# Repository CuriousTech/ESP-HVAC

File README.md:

# ESP-HVAC (ESP8266 & ESP-32)
WiFi Smart Omniscient HVAC Touchscreen Theromstat  

This project is discontinued (except for bugfixes and support code changes). New work will be on 
[WT32-SC01-HVAC](https://github.com/CuriousTech/WT32-SC01-HVAC)  

<b>2018 Model:</b> The new model was redesigned with a cooler switching regulator (~20mA idle, with a dim screen), smaller ($16.50 from OSHPark) more options for the temp/RH sensor, and the rotory encoder was removed, but has a header for an external encoder or buttons. The only difference in connections is the SCL/SDA were accidentaly reversed on the onboard SHTxx chip. Pics should be at the bottom.  

Notes about the Nextion: The baudrate is bauds=115200 in the main initialize varaibles. This will allow it to communicate at the highest speed.  

The "Basic" (Discovery model works without modification) has a 10K pullduown resistor for 5V tolerance (R13: next to the connector).  Removing this allows the ESP8266 to boot normally and operate without any resistors added, or add a 10K pullup between TX and 3V3 when serial debug is not connected.  I've opted for the removal of the resistor, which fixes all problems.  The 5K6 on the thermostat (R17) allowed it to operate with serial connected plus the pulldown, but not without.  The blue wire (data sent to the ESP) doesn't really need any resistors.  The ESP can't be programmed without a 1K while both are connected, and with the 1K and debug the touchscreen won't work.  So just disconnect the wire while programming and reconnect it after.  

This has replaced the old Spark-O-Stat with a newer system using the ESP-07 (now ESP32), with a better screen (Nextion HMI 2.8" touchscreen), 5 outputs (1 extra output for humidifier), option for SHT21 (I2C) or DHT22/11, AM2302/22, and anolog input for expansion.  

Main and remote units are designed into the single PCB with wired 5V or USB Mini-B for the remote units, and 24VAC for main.  Headers on top are for onboard serial programming of the ESP and Nextion.  Only power it with 1 source at a time. (3V3 for just the ESP, encoder, and temp sensor, 5V to include the display, or 24VAC for all of it including the SSRs). Add the switching regulator to the remote for battery power (6-40V).   

<b>Remote:</b> By tapping the target temperature on the display, it will toggle transmitting the remote temperature and humidity to the main unit to use in all operations.  Tapping the same item on the main unit will also end the remote temperature connection.  There are notifications to indicate use as well as a flashing run indicator instead of solid.  

Some screens including a keyboard and SSID chooser, but this is using the auto connect with SoftAP server (which attempts to find the stored SSID while waiting on input) so it should never be needed.  The dimmed screensaver will change to a clock, and a few other odd displays over time.  

Cool/heat low/high:  
These are the desired temperature ranges for cooling and heating, which are calculated based on outside temperature over the next set number of days.  

Cycle:  
Disable heat and cool, but still cycles the fan by the Auto Fan: Run: settings. 4:00 and 5 default = 5 minutes every 4 hours.  

Threshold:  
The temperature offset to complete a cycle.  

Pre-cycle fan time:  
0 disables, 1 second to 5 minutes.  This is the first phase of the cycle.  When the temperature reaches the target, the fan is turned on to cycle air for the set time, which causes the thermostat to read a more overall temperature. If the threshold is reached before this ends, which it can, it will shut off. Otherwise it continues to the run phase, which runs for at least the cycleMin period to save wear on the compressor because this does shorten the run time considerably.  A good value to use is the time it takes to lower the temperature after turning the fan on before it plateaus.  Usually around 2 minutes.  

Post-cycle fan time:  
Runs fan after cycle completes.  This is the third phase of the cycle, which continues to push air through the cold radiator and ductwork.  2 minutes is good, but you can use an IR thermometer on a vent to see how long the cold air continues.  

Humidifier settings:  
Off: Always off  
Fan: Run when fan is on  
Run: Run when thermostat is running a cycle  
Auto1: Operate by humidistat during run cycles  
Auto2: Humidistat runs indepentantly of thermostat (shares fan control)  

Override:  
Use to heat or cool by a selected offset temperature for a specified time.  

Freshen:  
Starts the fan with a timeout.  This uses the post fan timer, so a normal cycle will cancel it.  

Idle min, cycle min/max:  
These are timers in seconds to control the thermstat operating limits.  Idle min is the shortest time between cycles.  Cycle min is the shortest time for a cycle, and max is the longest.  Be careful with these settings.  Running the compressor too short or too long can cause damage.  

Away time and temperature delta offset:  
The away time is in hours:minutes unlike the rest of the timers, but uses the override timer.  It can be turned on and off with the button, but will also turn off with the timer.  There are 2 temp values that are displayed depending on heat or cool mode.  One for heat and one for cool, like the pre/post fan.
Like any setting, it can be automated with something like Tasker.  To turn on would be <b>http://ip:85?key=password&away=1</b>  

Other settings:  
AC differential limit: Increases thermostat if inside/outside difference is more than 30. This assumes Fahrenheit. Change for Celcius.  
Heat Threshold: Heatpump will switch off and use gas when outside temp goes below set value (default 33). Change for Celcius.  
PKW (price per killawatt hour), CFM (gas cubic feet per minute), CCF (cost per 100 cubic foot): Set the PPKW and CCF based on billing. CFM is dependant on the furnace.  
FC Shift (in minutes): Shifts the forecast for the temperature adjust. Use the setting on the chart page (they don't affect the actual settings) to determine what's best. There are 2 values for heat and cool here as well.   

The web chart.  Dark gray is off, cyan is fan running, blue is compressor+fan, NG is red, HP is yellow, rh is green, the target/threshold is the wave.  The thermostat is in the hottest room in the house, so it does look warmer than it really is, but that's why there's a remote unit, and now multiple sensors.  

New Model
  
Remote (this uses only a few components: the 3.3V regulator, 3 capacitors, USB connector, temp sensor, and 7 required resistors)  

Sensor web page

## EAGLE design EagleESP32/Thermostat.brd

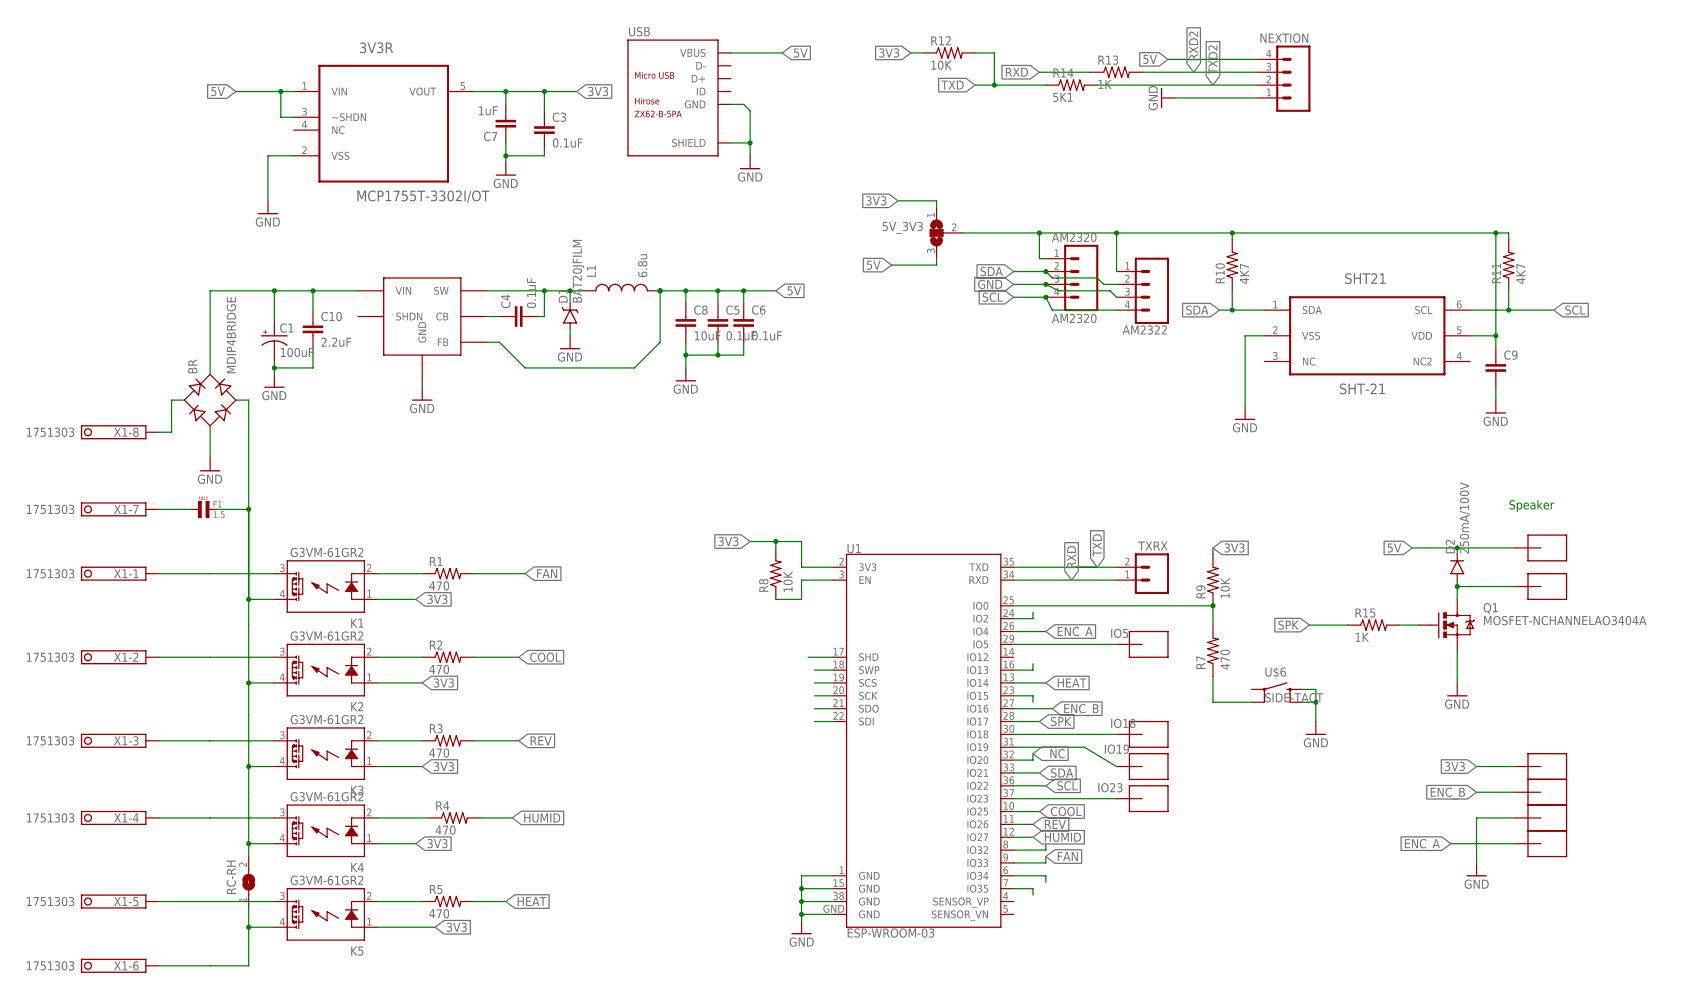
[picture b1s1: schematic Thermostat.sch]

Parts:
3V3R: MCP1755T-3302I/OT; SOT95P270X145-5N
5V_3V3: SJ2W; SJ_2
AM2320: AM2320; 1X04
AM2322: CONN_041.27MM; 1X04_1.27MM
BR: MDIP4BRIDGE; MICRODIP4
C1: 100uF; PANASONIC_C
C3, C4, C5, C6: 0.1uF; 0805
C7: 1uF; 0805
C8: 10uF; 0805
C9: CAP0603-CAP; 0603-CAP
C10: 2.2uF; 0805
D1: BAT20JFILM; SOD-323
D2: 250mA/100V; SOD-323
F1: 1.5; L4,8
K1, K2, K3, K4, K5: G3VM-61GR2; SOP04
L1: 6.8u; 1007
NEXTION: M04PTH; 1X04
Q1: MOSFET-NCHANNELAO3404A; SOT23-3
R1, R2, R3, R4, R5, R7: 470; 0805
R8, R9, R12: 10K; 0805
R10, R11: 4K7; 0805
R13, R15: 1K; 0805
R14: 5K1; 0805
RC-RH: SJ
SHT21: SHT-21; SHT21
TXRX: M02PTH; 1X02
U1: ESP-WROOM-03
U$1, U$2, U$3, U$4: SMD-PAD182X64; SMD-PAD1
U$5, U$7, U$8, U$9, U$10, U$11: SMD-PAD1SMD-PAD80X32; SMD-PAD6
U$6: SIDE-TACT
USB: ZX62-B-5PA; MICRO-USB5+6P-SMD-0.65-AB
VREG: LMR16006YQ; SOT-23-6
X1: 1751303

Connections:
3V3: 3V3R.5 (VOUT), 5V_3V3.1, C3.1, C7.2, K1.1 (A), K2.1 (A), K3.1 (A), K4.1 (A), K5.1 (A), R8.2, R9.2, R12.1, U1.2 (3V3), U$7.>PAD
5V: 3V3R.1 (VIN), 3V3R.3 (~SHDN), 5V_3V3.3, C5.1, C6.1, C8.1, D2.C, L1.2, NEXTION.4, U$5.>PAD, USB.1 (VBUS), VREG.3 (FB)
COOL: R2.2, U1.10 (IO25)
ENC_A: U1.26 (IO4), U$10.>PAD
ENC_B: U1.27 (IO16), U$8.>PAD
FAN: R1.2, U1.9 (IO33)
GND: 3V3R.2 (VSS), AM2320.3, AM2322.3, BR.-, C1.-, C3.2, C5.2, C6.2, C7.1, C8.2, C9.2, C10.2, D1.A, NEXTION.1, Q1.2 (S), SHT21.2 (VSS), U1.1 (GND), U1.15 (GND), U1.38 (GND), U1.GND, U$6.3 (2), U$6.4, U$9.>PAD, USB.5 (GND), USB.P1 (SHIELD), USB.P2 (SHIELD), USB.P3 (SHIELD), USB.P4 (SHIELD), USB.P5 (SHIELD), USB.P6 (SHIELD), VREG.2 (GND)
HEAT: R5.2, U1.13 (IO14)
HUMID: R4.2, U1.12 (IO27)
IO5: U1.29 (IO5), U$3.>PAD
IO18: U1.30 (IO18), U$4.>PAD
IO19: U1.31 (IO19), U$1.>PAD
IO23: U1.37 (IO23), U$2.>PAD
unnamed: C4.2, D1.C, L1.1, VREG.6 (SW)
unnamed: BR.AC2, F1.P$2 (2), K1.4 (DS1), K2.4 (DS1), K3.4 (DS1), K4.4 (DS1), RC-RH.2
unnamed: K4.2 (K), R4.1
unnamed: Q1.1 (G), R15.2
unnamed: K3.2 (K), R3.1
unnamed: R8.1, U1.3 (EN)
unnamed: K2.2 (K), R2.1
unnamed: K4.3 (DS2), X1.4
unnamed: K2.3 (DS2), X1.2
unnamed: R7.2, R9.1, U1.25 (IO0)
unnamed: K1.3 (DS2), X1.1
unnamed: K1.2 (K), R1.1
unnamed: C4.1, VREG.1 (CB)
unnamed: K5.3 (DS2), X1.5
unnamed: BR.AC1, X1.8
unnamed: K5.4 (DS1), RC-RH.1, X1.6
unnamed: F1.P$1 (1), X1.7
unnamed: BR.+, C1.+, C10.1, VREG.5 (VIN)
unnamed: K5.2 (K), R5.1
unnamed: R7.1, U$6.2 (3)
unnamed: K3.3 (DS2), X1.3
unnamed: D2.A, Q1.3 (D), U$11.>PAD
NC: SHT21.3 (NC)
PWR: 5V_3V3.2, AM2320.1, AM2322.1, C9.1, R10.2, R11.2, SHT21.5 (VDD)
REV: R3.2, U1.11 (IO26)
RXD: R13.1, TXRX.1, U1.34 (RXD)
RXD2: NEXTION.3, R13.2
SCL: AM2320.4, AM2322.4, R11.1, SHT21.6 (SCL), U1.36 (IO22)
SDA: AM2320.2, AM2322.2, R10.1, SHT21.1 (SDA), U1.33 (IO21)
SPK: R15.1, U1.28 (IO17)
TXD: R12.2, R14.1, TXRX.2, U1.35 (TXD)
TXD2: NEXTION.2, R14.2
_NC: U1.32 (IO20)

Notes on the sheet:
Speaker

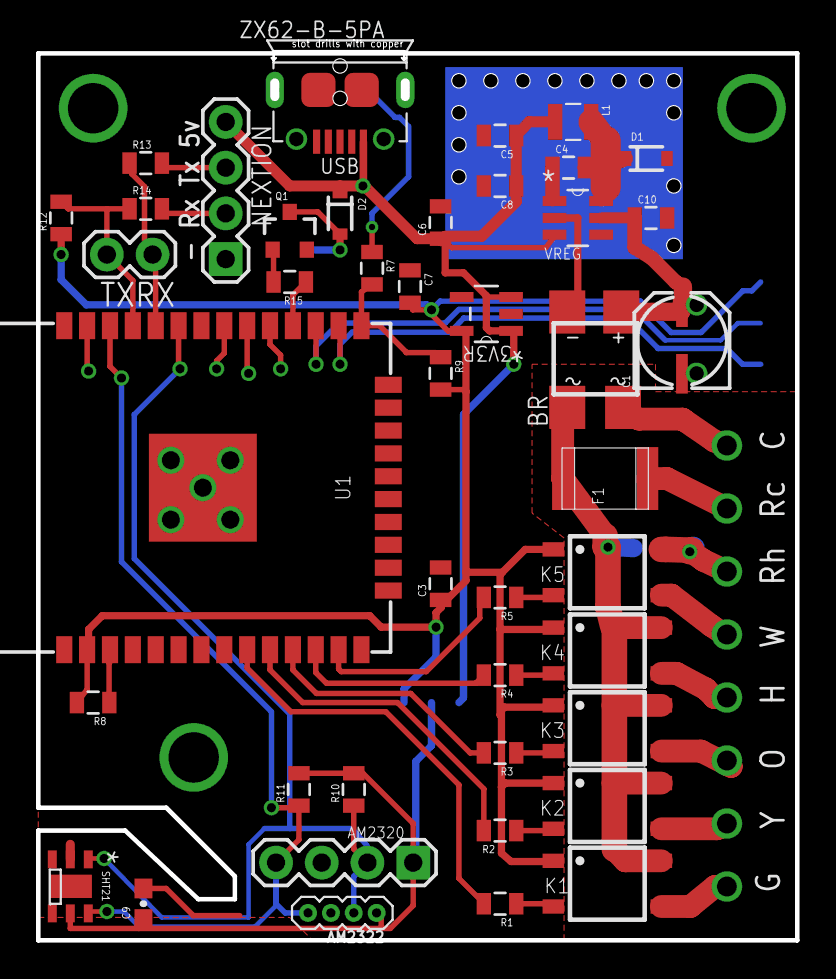
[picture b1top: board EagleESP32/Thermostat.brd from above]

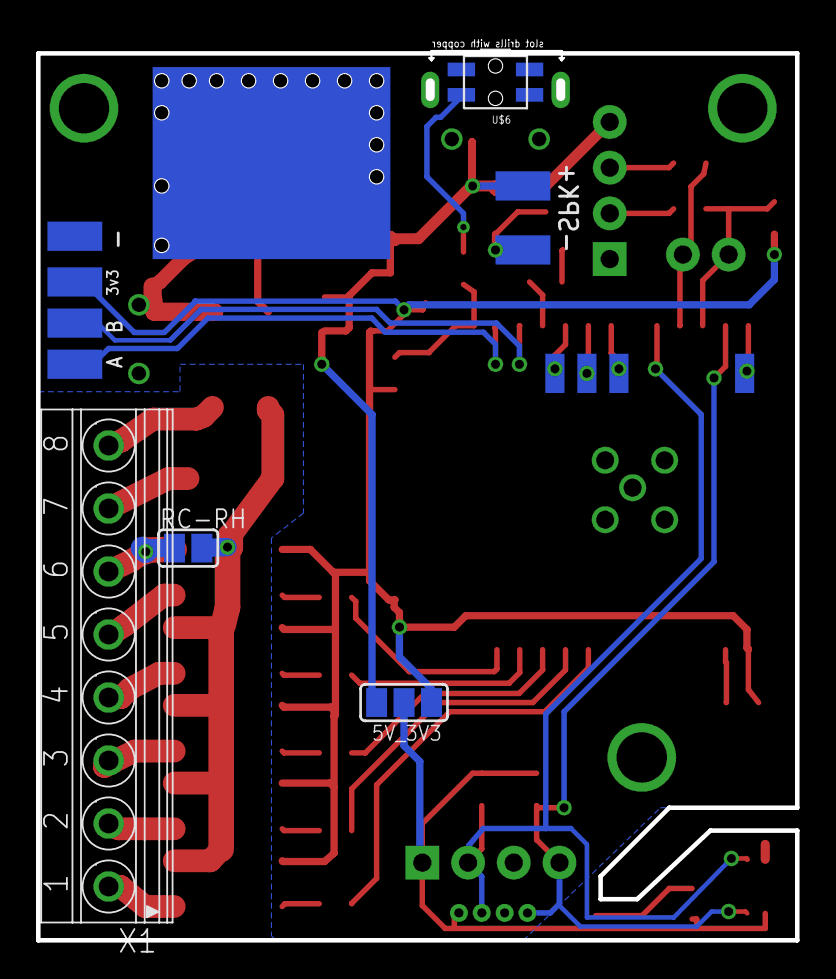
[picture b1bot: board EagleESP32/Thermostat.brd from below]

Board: 2 copper layers, 41.9 x 49.9 mm, 57 parts (14 on the bottom side), 44 nets.

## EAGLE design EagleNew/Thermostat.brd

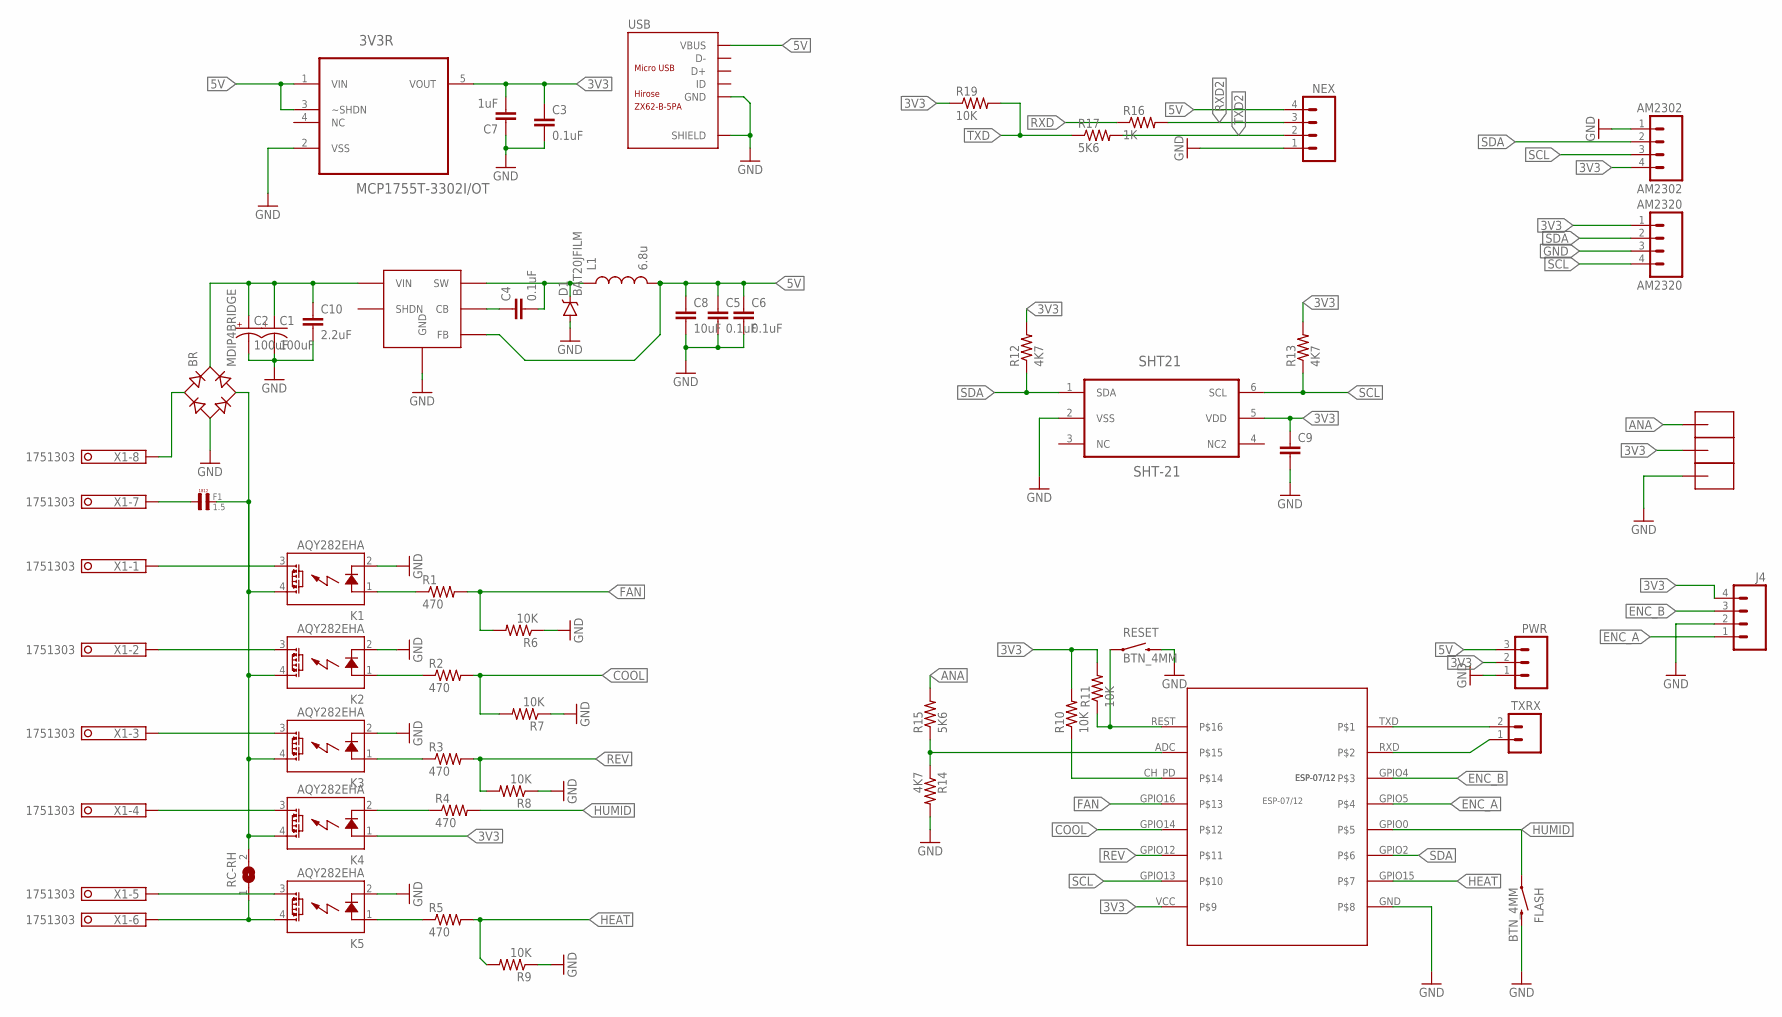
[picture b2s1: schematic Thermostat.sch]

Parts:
3V3R: MCP1755T-3302I/OT; SOT95P270X145-5N
AM2302: AM2302; 1X04
AM2320: AM2320; 1X04
BR: MDIP4BRIDGE; MICRODIP4
C1, C2: 100uF; PANASONIC_C
C3, C4, C5, C6: 0.1uF; 0805
C7: 1uF; 0805
C8: 10uF; 0805
C9: CAP0603-CAP; 0603-CAP
C10: 2.2uF; 0805
D1: BAT20JFILM; SOD-323
F1: 1.5; L4,8
FLASH: BTN_4MM
J4: M04PTH; 1X04
K1, K2, K3, K4, K5: AQY282EHA; SOP04
L1: 6.8u; 1007
NEX: M04PTH; 1X04
PWR: M03PTH; 1X03
R1, R2, R3, R4, R5: 470; 0805
R6, R7, R8, R9, R10, R11, R19: 10K; 0805
R12, R13, R14: 4K7; 0805
R15, R17: 5K6; 0805
R16: 1K; 0805
RC-RH: SJ
RESET: BTN_4MM
SHT21: SHT-21; SHT21
TXRX: M02PTH; 1X02
U$1: ESP-07/12
U$2, U$3, U$4: SMD-PAD182X64; SMD-PAD1
USB: ZX62-B-5PA; MICRO-USB5+6P-SMD-0.65-AB
VREG: LMR16006YQ; SOT-23-6
X1: 1751303

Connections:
3V3: 3V3R.5 (VOUT), AM2302.4, AM2320.1, C3.1, C7.2, C9.1, J4.4, K4.1 (A), PWR.2, R10.2, R11.2, R12.2, R13.2, R19.1, SHT21.5 (VDD), U$1.VCC, U$3.>PAD
5V: 3V3R.1 (VIN), 3V3R.3 (~SHDN), C5.1, C6.1, C8.1, L1.2, NEX.4, PWR.3, USB.1 (VBUS), VREG.3 (FB)
ADC: R14.1, R15.1, U$1.ADC
ANA: R15.2, U$4.>PAD
COOL: R2.2, R7.2, U$1.GPIO14
ENC_A: J4.1, U$1.GPIO5
ENC_B: J4.3, U$1.GPIO4
FAN: R1.2, R6.2, U$1.GPIO16
GND: 3V3R.2 (VSS), AM2302.1, AM2320.3, BR.-, C1.-, C2.-, C3.2, C5.2, C6.2, C7.1, C8.2, C9.2, C10.2, D1.A, FLASH.2, J4.2, K1.2 (K), K2.2 (K), K3.2 (K), K5.2 (K), NEX.1, PWR.1, R6.1, R7.1, R8.1, R9.1, R14.2, RESET.2, SHT21.2 (VSS), U$1.GND, U$2.>PAD, USB.5 (GND), USB.P1 (SHIELD), USB.P2 (SHIELD), USB.P3 (SHIELD), USB.P4 (SHIELD), USB.P5 (SHIELD), USB.P6 (SHIELD), VREG.2 (GND)
HEAT: R5.2, R9.2, U$1.GPIO15
HUMID: FLASH.1, R4.2, U$1.GPIO0
unnamed: K4.2 (K), R4.1
unnamed: C4.2, D1.C, L1.1, VREG.6 (SW)
unnamed: BR.AC2, F1.P$2 (2), K1.4 (DS1), K2.4 (DS1), K3.4 (DS1), K4.4 (DS1), RC-RH.2
unnamed: K1.1 (A), R1.1
unnamed: K2.1 (A), R2.1
unnamed: K3.1 (A), R3.1
unnamed: K4.3 (DS2), X1.4
unnamed: K2.3 (DS2), X1.2
unnamed: K1.3 (DS2), X1.1
unnamed: C4.1, VREG.1 (CB)
unnamed: K5.3 (DS2), X1.5
unnamed: BR.AC1, X1.8
unnamed: K5.4 (DS1), RC-RH.1, X1.6
unnamed: F1.P$1 (1), X1.7
unnamed: BR.+, C1.+, C2.+, C10.1, VREG.5 (VIN)
unnamed: K5.1 (A), R5.1
unnamed: K3.3 (DS2), X1.3
unnamed: R10.1, U$1.CH_PD
NC: SHT21.3 (NC)
REST: R11.1, RESET.1, U$1.REST
REV: R3.2, R8.2, U$1.GPIO12
RXD: R16.1, TXRX.1, U$1.RXD
RXD2: NEX.3, R16.2
SCL: AM2302.3, AM2320.4, R13.1, SHT21.6 (SCL), U$1.GPIO13
SDA: AM2302.2, AM2320.2, R12.1, SHT21.1 (SDA), U$1.GPIO2
TXD: R17.1, R19.2, TXRX.2, U$1.TXD
TXD2: NEX.2, R17.2

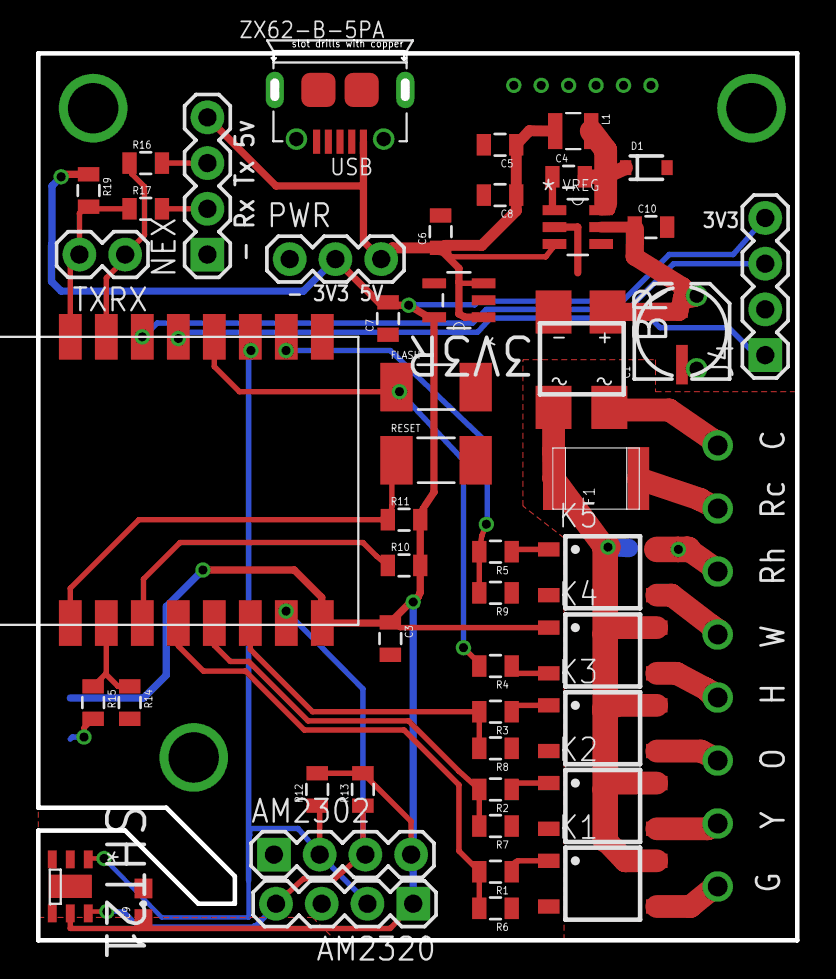
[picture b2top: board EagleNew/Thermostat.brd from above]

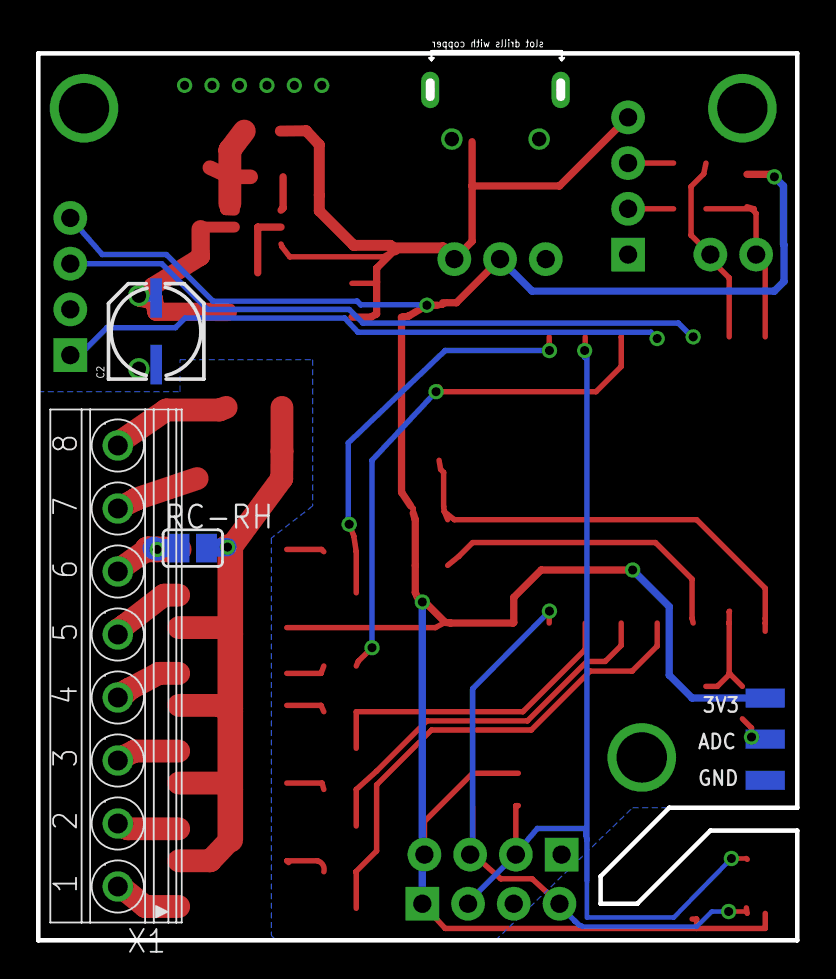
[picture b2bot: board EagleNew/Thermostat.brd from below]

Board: 2 copper layers, 41.9 x 49.9 mm, 55 parts (6 on the bottom side), 37 nets.

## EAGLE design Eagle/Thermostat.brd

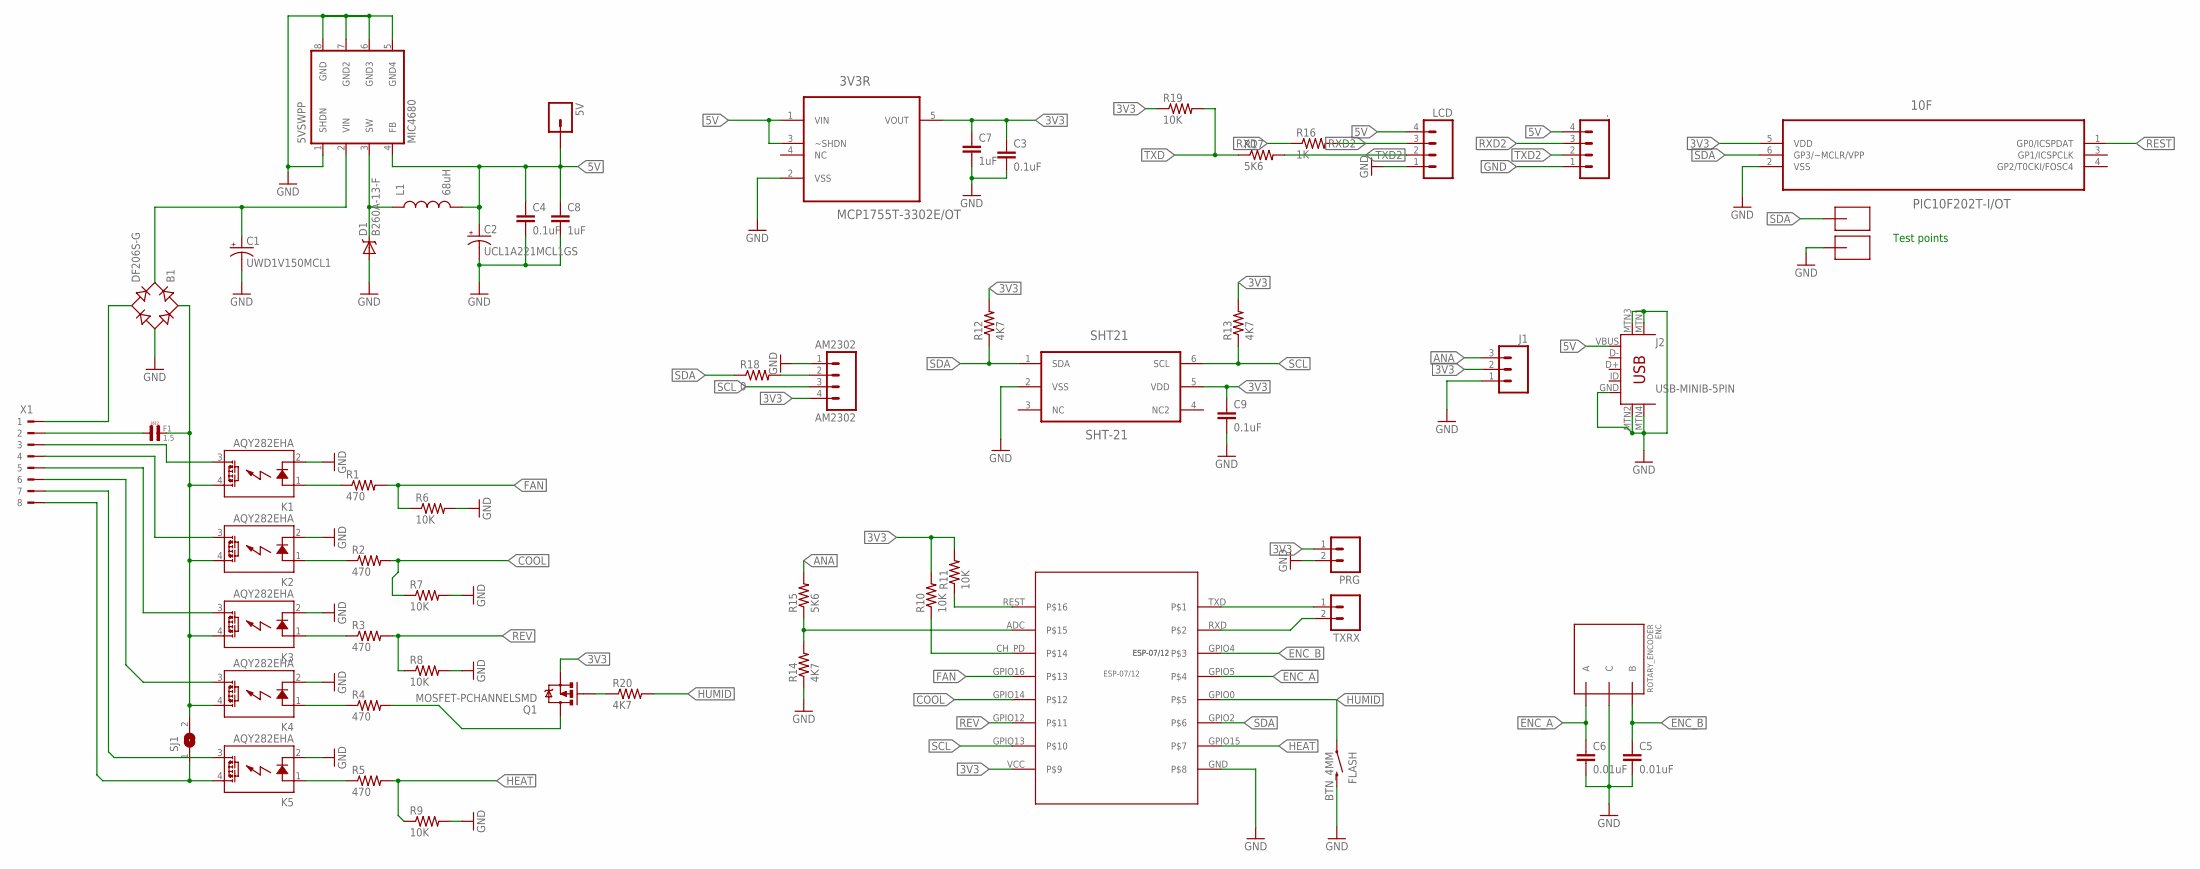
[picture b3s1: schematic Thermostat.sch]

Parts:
3V3R: MCP1755T-3302E/OT; SOT95P270X145-5N
5V: M01PTH; 1X01
5VSWPP: MIC4680; SO08
10F: PIC10F202T-I/OT; SOT95P270X145-6N
.: M04PTH; 1X04
AM2302: AM2302; 1X04
B1: DF206S-G; DFS
C1: UWD1V150MCL1; PANASONIC_C
C2: UCL1A221MCL1GS; PANASONIC_D
C3, C4, C9: 0.1uF; 0805
C5, C6: 0.01uF; 0805
C7, C8: 1uF; 0805
D1: B260A-13-F; SMA-DIODE
ENC: ROTARY_ENCODER; ROTORY_ENC
F1: 1.5; L4,8
FLASH: BTN_4MM
J1: M03PTH; 1X03
J2: USB-MINIB-5PIN; USB-MINIB
K1, K2, K3, K4, K5: AQY282EHA; SOP04
L1: 68uH; DR1030
LCD: M04PTH; 1X04
PRG: M02PTH; 1X02
Q1: MOSFET-PCHANNELSMD; SOT23-3
R1, R2, R3, R4, R5: 470; 0805
R6, R7, R8, R9, R10, R11, R19: 10K; 0805
R12, R13, R14, R20: 4K7; 0805
R15, R17: 5K6; 0805
R16: 1K; 0805
R18: 0; 0805
SHT21: SHT-21; SHT21
SJ1: SJ
TXRX: M02PTH; 1X02
U$1: ESP-07/12
U$2, U$5: SMD-PAD1
X1: 180-8

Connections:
3V3: 3V3R.5 (VOUT), 10F.5 (VDD), AM2302.4, C3.1, C7.1, C9.1, J1.2, PRG.1, Q1.2 (S), R10.2, R11.2, R12.2, R13.2, R19.1, SHT21.5 (VDD), U$1.VCC
5V: 3V3R.1 (VIN), 3V3R.3 (~SHDN), 5V.1, 5VSWPP.4 (FB), ..4, C2.+, C4.1, C8.1, J2.VBUS, L1.2, LCD.4
ADC: R14.2, R15.1, U$1.ADC
ANA: J1.3, R15.2
COOL: R2.2, R7.1, U$1.GPIO14
ENC_A: C6.1, ENC.A, U$1.GPIO5
ENC_B: C5.1, ENC.B, U$1.GPIO4
FAN: R1.2, R6.1, U$1.GPIO16
GND: 3V3R.2 (VSS), 5VSWPP.1 (SHDN), 5VSWPP.5 (GND4), 5VSWPP.6 (GND3), 5VSWPP.7 (GND2), 5VSWPP.8 (GND), 10F.2 (VSS), ..1, AM2302.1, B1.-, C1.-, C2.-, C3.2, C4.2, C5.2, C6.2, C7.2, C8.2, C9.2, D1.A, ENC.C, FLASH.2, J1.1, J2.GND, J2.MTN1 (MTN2), J2.MTN2 (MTN3), J2.MTN3 (MTN1), J2.MTN4, K1.2 (K), K2.2 (K), K3.2 (K), K4.2 (K), K5.2 (K), LCD.1, PRG.2, R6.2, R7.2, R8.2, R9.2, R14.1, SHT21.2 (VSS), U$1.GND, U$2.>NAME
HEAT: R5.2, R9.1, U$1.GPIO15
HUMID: FLASH.1, R20.2, U$1.GPIO0
unnamed: Q1.1 (G), R20.1
unnamed: 5VSWPP.3 (SW), D1.C, L1.1
unnamed: B1.AC1, F1.P$2 (2), K1.4 (DS1), K2.4 (DS1), K3.4 (DS1), K4.4 (DS1), SJ1.2
unnamed: K1.1 (A), R1.1
unnamed: K2.1 (A), R2.1
unnamed: Q1.3 (D), R4.2
unnamed: K3.1 (A), R3.1
unnamed: K4.3 (DS2), X1.6
unnamed: K2.3 (DS2), X1.4
unnamed: K4.1 (A), R4.1
unnamed: K1.3 (DS2), X1.3
unnamed: AM2302.2, R18.2
unnamed: K5.3 (DS2), X1.7
unnamed: B1.AC2, X1.1
unnamed: 5VSWPP.2 (VIN), B1.+, C1.+
unnamed: K5.1 (A), R5.1
unnamed: K5.4 (DS1), SJ1.1, X1.8
unnamed: K3.3 (DS2), X1.5
unnamed: R10.1, U$1.CH_PD
unnamed: F1.P$1 (1), X1.2
NC: SHT21.3 (NC)
REST: 10F.1 (GP0/ICSPDAT), R11.1, U$1.REST
REV: R3.2, R8.1, U$1.GPIO12
RXD: R16.1, TXRX.2, U$1.RXD
RXD2: ..3, LCD.3, R16.2
SCL: AM2302.3, R13.1, SHT21.6 (SCL), U$1.GPIO13
SDA: 10F.6 (GP3/~MCLR/VPP), R12.1, R18.1, SHT21.1 (SDA), U$1.GPIO2, U$5.>NAME
TXD: R17.1, R19.2, TXRX.1, U$1.TXD
TXD2: ..2, LCD.2, R17.2

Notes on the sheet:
Test points

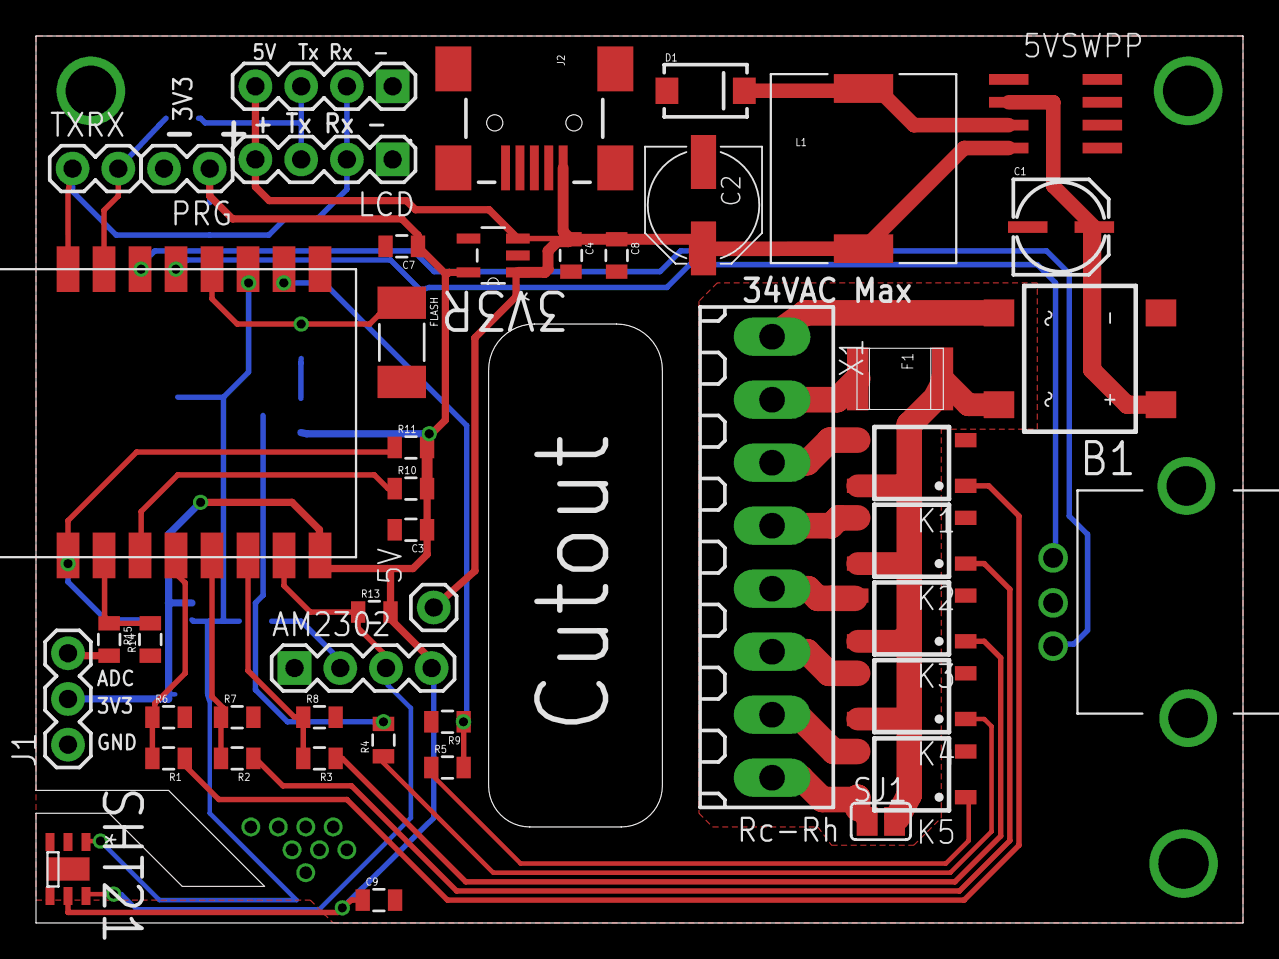
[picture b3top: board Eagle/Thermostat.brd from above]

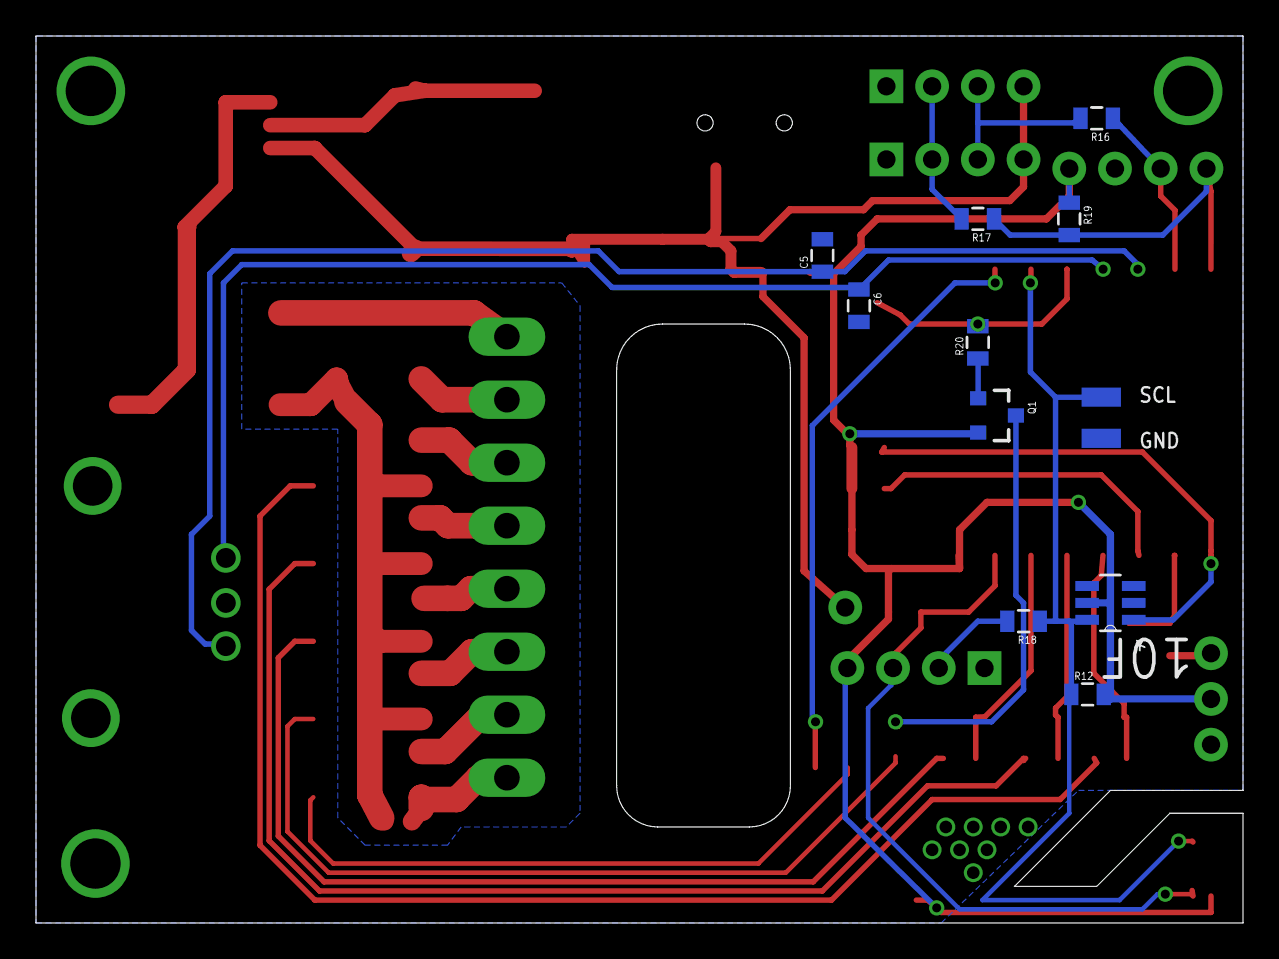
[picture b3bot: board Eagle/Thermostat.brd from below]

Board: 2 copper layers, 67.1 x 49.3 mm, 58 parts (12 on the bottom side), 39 nets.

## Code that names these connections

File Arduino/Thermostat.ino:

/**The MIT License (MIT)

Copyright (c) 2016 by Greg Cunningham, CuriousTech

Permission is hereby granted, free of charge, to any person obtaining a copy
of this software and associated documentation files (the "Software"), to deal
in the Software without restriction, including without limitation the rights
to use, copy, modify, merge, publish, distribute, sublicense, and/or sell
copies of the Software, and to permit persons to whom the Software is
furnished to do so, subject to the following conditions:

The above copyright notice and this permission notice shall be included in all
copies or substantial portions of the Software.

THE SOFTWARE IS PROVIDED "AS IS", WITHOUT WARRANTY OF ANY KIND, EXPRESS OR
IMPLIED, INCLUDING BUT NOT LIMITED TO THE WARRANTIES OF MERCHANTABILITY,
FITNESS FOR A PARTICULAR PURPOSE AND NONINFRINGEMENT. IN NO EVENT SHALL THE
AUTHORS OR COPYRIGHT HOLDERS BE LIABLE FOR ANY CLAIM, DAMAGES OR OTHER
LIABILITY, WHETHER IN AN ACTION OF CONTRACT, TORT OR OTHERWISE, ARISING FROM,
OUT OF OR IN CONNECTION WITH THE SOFTWARE OR THE USE OR OTHER DEALINGS IN THE
SOFTWARE.
*/

// Build with Arduino IDE 1.8.19
//  ESP8266 (3.1.1)  1MB (FS:64Kb)
//  ESP32: (2.0.6) ESP Dev Module, 115200 baud, 80MHz (WiFi/BT) or any speed, QIO, Default 4MB with spiffs
// For remote unit, uncomment #define REMOTE in HVAC.h

#include <ESPAsyncWebServer.h> // https://github.com/me-no-dev/ESPAsyncWebServer
#include <TimeLib.h> // http://www.pjrc.com/teensy/td_libs_Time.html
#include <UdpTime.h> // https://github.com/CuriousTech/ESP07_WiFiGarageDoor/tree/master/libraries/UdpTime
#include "HVAC.h"
#include "Encoder.h"
#include "WebHandler.h"
#include "display.h"
#include <Wire.h>
#include "eeMem.h"
#include "RunningMedian.h"

// ESP8266 uncomment to swap Serial's pins to 15(TX) and 13(RX) that don't interfere with booting
//#define SER_SWAP https://github.com/esp8266/Arduino/blob/master/doc/reference.md

// Uncomment only one of these
#include <SHT21.h> // //Libraries/SHT21
//#include <DHT.h>  // http://www.github.com/markruys/arduino-DHT
//#include <DallasTemperature.h> //DallasTemperature from library mamanger
//#include <AM2320.h> // //Libraries/AM2320

//----- Pin Configuration - See HVAC.h for the rest -
#ifdef ESP32
#define SDA      21
#define SCL      22
#define ENC_A    16
#define ENC_B    4
#else // ESP8266 pins
#define SDA      2
#define SCL      13
#define ENC_A    5  // Encoder is on GPIO4 and 5
#define ENC_B    4
#endif
//------------------------

Display display;
eeMem ee;

HVAC hvac;

RunningMedian<int16_t,25> tempMedian; //median of 25 samples

#ifdef SHT21_H
SHT21 sht(SDA, SCL, 4);
#endif
#ifdef dht_h
DHT dht;
#endif
#ifdef DallasTemperature_h
const int ds18Resolution = 12;
DeviceAddress ds18addr = { 0x28, 0xC1, 0x02, 0x64, 0x04, 0x00, 0x00, 0x35 };
unsigned int ds18delay;
unsigned long ds18lastreq = 1; //zero is special
const unsigned int ds18reqdelay = 5000; //request every 5 seconds
unsigned long ds18reqlastreq;
OneWire oneWire(2); //pin 2
DallasTemperature ds18(&oneWire);
#endif
#ifdef AM2303_H
AM2320 am;
#endif

UdpTime uTime;

Encoder rot(ENC_B, ENC_A);

extern void WsSend(String s);

bool EncoderCheck()
{
  if(ee.b.bLock) return false;

  int r = rot.poll();

  if(r == 0)  // no change
    return false;

  display.screen(true); // ensure page is thermostat

  int8_t m = (display.m_adjustMode < 2) ? Mode_Cool : Mode_Heat; // lower 2 are cool
  int8_t hilo = (display.m_adjustMode ^ 1) & 1; // hi or low of set
  int16_t t = hvac.getSetTemp(m, hilo ); // 

  t += r; // inc/dec by any amount

  hvac.setTemp(m, t, hilo);

  if(hvac.m_bLink) // adjust both high and low
  {
    t = hvac.getSetTemp(m, hilo^1 ) + r; // adjust opposite hi/lo the same
    hvac.setTemp(m, t, hilo^1);
  }

  display.updateTemps();
  return true;
}

void setup()
{
  Serial.begin(115200);  // Nextion must be set with bauds=115200
#ifdef SER_SWAP
  Serial.swap(); //swap to gpio 15/13
#endif
  ee.init();
  hvac.init();
  display.init();
  startServer();

#ifdef SHT21_H
  sht.init();
#endif
#ifdef dht_h
  dht.setup(SCL, DHT::DHT22);
#endif
#ifdef DallasTemperature_h
  ds18.setResolution(ds18addr, ds18Resolution);
  ds18.setWaitForConversion(false); //this enables asyncronous calls
  ds18.requestTemperatures(); //fire off the first request
  ds18lastreq = millis();
  ds18delay = 750 / (1 << (12 - ds18Resolution)); //delay based on resolution
#endif
#ifdef AM2303_H
  am.begin(SDA, SCL);
#endif
}

void loop()
{
  static uint8_t hour_save, min_save = 255, sec_save;
  static int8_t lastSec;
  static int8_t lastHour;
  static int8_t lastDay = -1;

  while( EncoderCheck() );
  display.checkNextion();  // check for touch, etc.
  if(uTime.check(ee.tz))
  {
    hvac.m_DST = uTime.getDST();
    if(lastDay == -1)
      lastDay = day() - 1;
  }
  handleServer(); // handles mDNS, web
#ifdef SHT21_H
  if(sht.service())
  {
    tempMedian.add((ee.b.bCelcius ? sht.getTemperatureC():sht.getTemperatureF()) * 10);
    float temp;
    if (tempMedian.getAverage(2, temp) == tempMedian.OK) {
      hvac.updateIndoorTemp( temp, sht.getRh() * 10 );
    }
  }
#endif
#ifdef DallasTemperature_h
  if(ds18lastreq > 0 && millis() - ds18lastreq >= ds18delay) { //new temp is ready
    tempMedian.add((ee.b.bCelcius ? ds18.getTempC(ds18addr):ds18.getTempF(ds18addr)) );
    ds18lastreq = 0; //prevents this block from firing repeatedly
    float temp;
    if (tempMedian.getAverage(temp) == tempMedian.OK) {
      hvac.updateIndoorTemp( temp * 10, 500); //fake 50%
    }
  }

  if(millis() - ds18reqlastreq >= ds18reqdelay) {
    ds18.requestTemperatures(); 
    ds18lastreq = millis();
    ds18reqlastreq = ds18lastreq;
  }
#endif
  if(sec_save != second()) // only do stuff once per second
  {
    sec_save = second();
    if(secondsServer()) // once per second stuff, returns true once on connect
      uTime.start();
    display.oneSec();
    hvac.service();   // all HVAC code

#ifdef dht_h
    static uint8_t read_delay = 2;
    if(--read_delay == 0)
    {
      float temp;
      if(ee.bCelcius)
        temp = dht.getTemperature() * 10;
      else
        temp = dht.toFahrenheit(dht.getTemperature()) * 10;

      if(dht.getStatus() == DHT::ERROR_NONE)
      {
        tempMedian.add(temp);
        if (tempMedian.getAverage(2, temp) == tempMedian.OK) {
          hvac.updateIndoorTemp( temp, dht.getHumidity() * 10);
        }
      }
      read_delay = 5; // update every 5 seconds
    }
#endif
#ifdef AM2303_H
    static uint8_t read_delay = 2;
    if(--read_delay == 0)
    {
      float temp;
      float rh;
      if(am.measure(temp, rh))
      {
        if(!ee.b.bCelcius)
          temp = temp * 9 / 5 + 32;
        tempMedian.add(temp * 10);
        if (tempMedian.getAverage(2, temp) == tempMedian.OK) {
          hvac.updateIndoorTemp( temp, rh * 10 );
        }
      }
      read_delay = 5; // update every 5 seconds
    }
#endif

    if(min_save != minute()) // only do stuff once per minute
    {
      min_save = minute();

      if(hour_save != hour()) // update our IP and time daily (at 2AM for DST)
      {
        hour_save = hour();
        if(hour_save == 2)
          uTime.start(); // update time daily at DST change
        if(hour_save == 0 && year() > 2020)
        {
          if(lastDay != -1)
          {
            hvac.dayTotals(lastDay);
            hvac.monthTotal(month() - 1, day());
          }
          lastDay = day() - 1;
          ee.iSecsDay[lastDay][0] = 0; // reset
          ee.iSecsDay[lastDay][1] = 0;
          ee.iSecsDay[lastDay][2] = 0;
          if(lastDay == 0) // new month
          {
            int m = (month() + 10) % 12; // last month: Dec = 10, Jan = 11, Feb = 0
            hvac.monthTotal(m, -1);
          }
        }
        if(ee.check())
        {
          if((hour_save & 1) == 0) // every other hour
          {
            ee.filterMinutes = hvac.m_filterMinutes;
            ee.update();
          }
        }
      }
    }

  }
  delay(9); // rotary encoder and lines() need 8ms minimum
}

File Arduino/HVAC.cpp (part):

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
    if(m_furnaceFan)      // fake fan status for furnace fan
      m_furnaceFan--;
    m_fanIdleTimer = 0;   // fan auto run timer reset
  }

  if(ee.b.Mode && !m_bRunning && !m_bFanRunning)
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  if(m_bStart && !m_bRunning)             // Start signal occurred
  {
    m_bStart = false;
    m_fanAutoRunTimer = 0; // disable fan autorun

    switch(mode)
    {
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  {
    m_iSecs[2] += m_fanOnTimer;
    costAdd(m_fanOnTimer, Mode_Fan, 0);
    m_fanOnTimer = 0;       // reset fan on timer
    humidSwitch(false);
  }
}
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      break;
    case 25: // awaydelta
      if(ee.b.Mode == Mode_Heat)
        ee.awayDelta[1] = constrain(val, (ee.b.bCelcius ? -83:-150), 0); // Limit to -15 degrees (heat away) target is constrained in calcTargetTemp
      else
        ee.awayDelta[0] = constrain(val, 0, (ee.b.bCelcius ? 83:150) ); // Limit +15 degrees (cool away)
      break;
    case 26: // away (uses the override feature)
      if(val) // away
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

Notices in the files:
Arduino/HVAC.cpp:
Copyright 2014 Greg Cunningham, CuriousTech.net
This library is free software; you can redistribute it and/or modify it under the terms of the GNU GPL 2.1 or later.
parts and their libraries:
SparkFun-Connectors: Licensing: CC v3.0 Share-Alike You are welcome to use this library for commercial purposes.
SparkFun-Resistors: Licensing: Creative Commons ShareAlike 4.0 International - https://creativecommons.org/licenses/by-sa/4.0
